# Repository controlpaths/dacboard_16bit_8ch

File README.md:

# 8CH DAC Board (16 bits)

Many times we need to obtain an analog signal from an embedded system. In these cases we will need a digital to analog converter. This board features two 4 channel digital to analog converters with a resolution of 16 bits. 

The output voltage of the board has a range from -10 volt to 10 volts qith a supply voltage of +-12V.

## Analog output

The DAC used in this board is the [DAC80004](https://www.ti.com/product/es-mx/DAC80004), a 4 channel, 16 bits DAC from Texas Instruments. This DAC is footprint compatible with DAC70004 (14 bits), and DAC60004 (12 bits).

To obtain the bipolar output, a simple circuit with just one amplifier is used. 

## Voltage reference

For the output range of +-10V, we will need a voltage reference of 2.5 volts. We can reduce the output range, and therefore increase the resolution in volts by using a reference of 1.024 volts or 1.250.

The reference used is the REF5020 with soma capacitors for fixeliminate the noise in the output voltage.

## Connectors

The conenctor are the only component in the bottom side of the board. The board uses three connectors, one for the control of the DAC, and two for the output voltages.

## Layout

The layout of the board is 35mm x 50mm. Several VCC planes and GND planes are used in the board to share the power supplies.

## Get Yours

This DAC Board is open-source, so you can use the output files to build your own in [JLCPCB](https://jlcpcb.com/?from=controlpath). You just need to compress the `gerber` directory, and upload it to [JLCPCB](https://jlcpcb.com/?from=controlpath). 

Remember to change the Surface Finish to **LeadFree HASL** to make your board ROHS compliant.

Then you have to add the PCB Assembly service and upload the [centroid](./kicad/production_files/dac16bit_8ch-all-pos.csv) file, and the [BOM](./kicad/production_files/bom.csv).

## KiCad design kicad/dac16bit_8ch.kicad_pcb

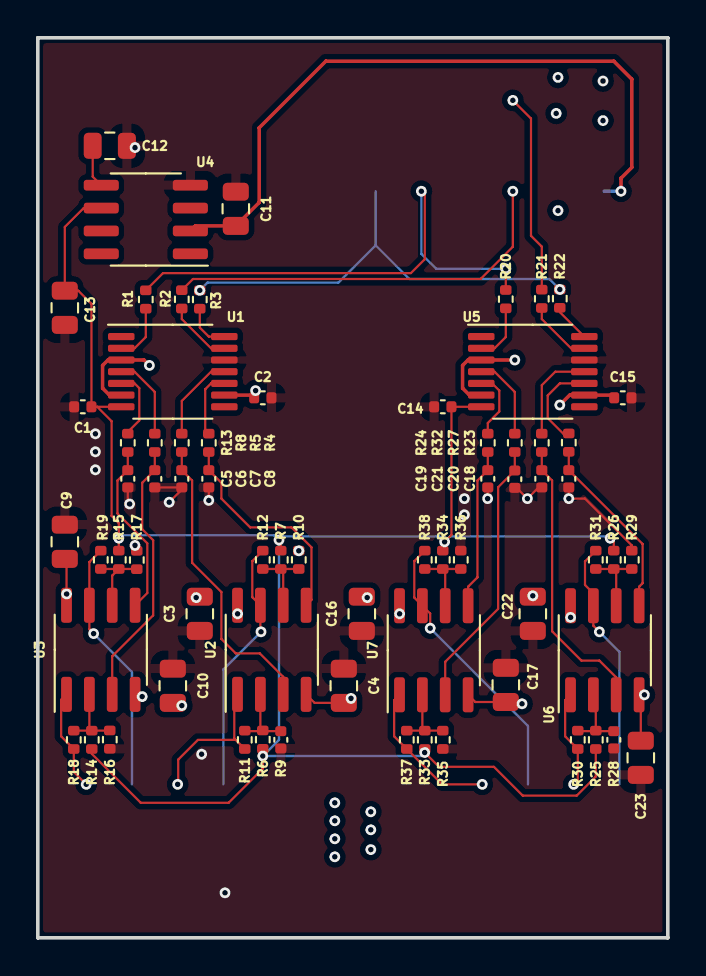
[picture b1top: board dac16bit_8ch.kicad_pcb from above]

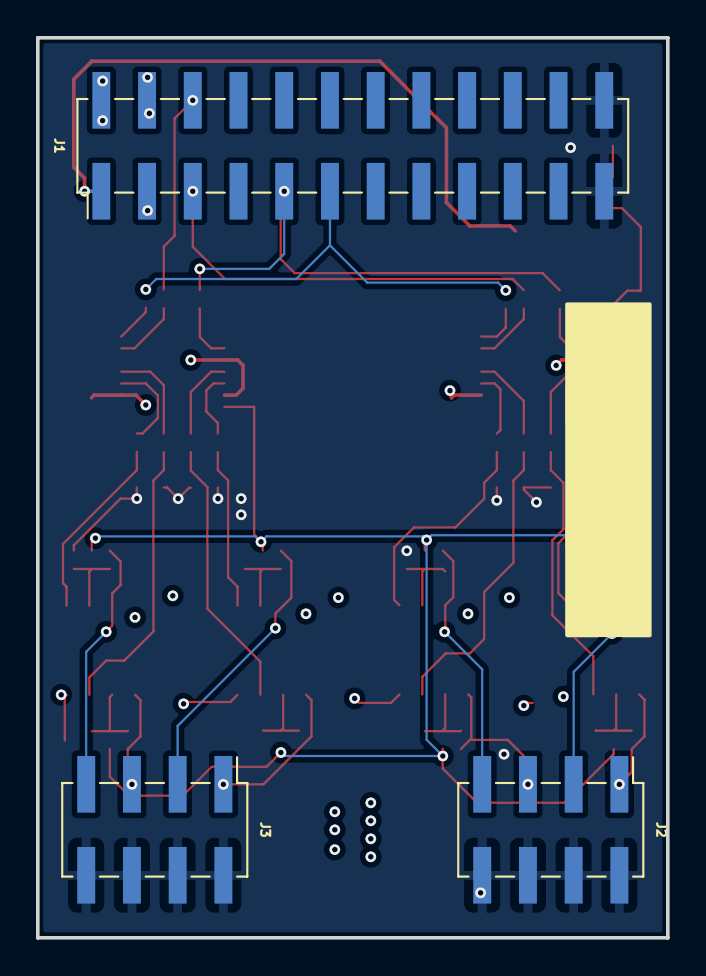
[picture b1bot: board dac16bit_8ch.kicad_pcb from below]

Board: 4 copper layers, 35.0 x 50.0 mm, 71 parts (3 on the bottom side), 49 nets.

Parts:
C1, C2, C14, C15: 100n; C_0402_1005Metric
C3, C4, C9, C10, C12, C16, C17, C22, C23: 100n; C_0805_2012Metric
C5, C6, C7, C8, C18, C19, C20, C21: 1n; C_0402_1005Metric
C11, C13: 1u; C_0805_2012Metric
J1: Conn_02x12_Odd_Even; PinHeader_2x12_P2.54mm_Vertical_SMD
J2, J3: Conn_02x04_Odd_Even; PinHeader_2x04_P2.54mm_Vertical_SMD
R1, R2, R3, R20, R21, R22: 100; R_0402_1005Metric
R4, R5, R8, R13, R23, R24, R27, R32: 4k7; R_0402_1005Metric
R6, R7, R14, R15, R25, R26, R33, R34: 8.25k; R_0402_1005Metric
R9, R28: 11k; C_0402_1005Metric
R10, R16, R17, R29, R35, R36: 11k; R_0402_1005Metric
R11, R12, R18, R19, R30, R31, R37, R38: 33k; R_0402_1005Metric
U1, U5: dacx0004; TSSOP-14_4.4x5mm_P0.65mm
U2, U3, U6, U7: OPA2188; SOIC-8_3.9x4.9mm_P1.27mm
U4: REF5025AD; SOIC-8_3.9x4.9mm_P1.27mm

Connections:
+3V3: C2.1, C15.1, J1.3, U1.3 (VDD), U1.6 (POR), U1.9 (~CLR), U5.3 (VDD), U5.6 (POR), U5.9 (~CLR)
+5V: C11.2, J1.1, U4.2 (Vin)
+12V: C3.2, C9.2, C16.2, C22.2, J1.2, U2.8 (V+), U3.8 (V+), U6.8 (V+), U7.8 (V+)
-12V: C4.2, C10.2, C17.2, C23.2, J1.4, U2.4 (V-), U3.4 (V-), U6.4 (V-), U7.4 (V-)
/dac0/vout_a_dac: C8.2, R13.2, U3.5 (+)
/dac0/vout_b_dac: C7.2, R8.2, U3.3 (+)
/dac0/vout_c_dac: C6.2, R5.2, U2.3 (+)
/dac0/vout_d_dac: C5.2, R4.2, U2.5 (+)
/dac1/vout_a_dac: C21.2, R32.2, U7.3 (+)
/dac1/vout_b_dac: C20.2, R27.2, U6.3 (+)
/dac1/vout_c_dac: C19.2, R24.2, U7.5 (+)
/dac1/vout_d_dac: C18.2, R23.2, U6.5 (+)
AO_CH0+: J2.1, R18.1, U3.1
AO_CH1+: J2.3, R19.1, U3.7
AO_CH2+: J2.5, R11.1, U2.1
AO_CH3+: J2.7, R12.1, U2.7
AO_CH4+: J3.1, R37.1, U7.1
AO_CH5+: J3.3, R38.1, U7.7
AO_CH6+: J3.5, R30.1, U6.1
AO_CH7+: J3.7, R31.1, U6.7
CLK_DAC: J1.11, R3.1, R22.1
CS_DAC: J1.9, R1.1, R20.1
GND: C1.2, C2.2, C3.1, C4.1, C5.1, C6.1, C7.1, C8.1, C9.1, C10.1, C11.1, C12.2, C13.2, C14.2, C15.2, C16.1, C17.1, C18.1, C19.1, C20.1, C21.1, C22.1, C23.1, J1.23, J1.24, J2.2, J2.4, J2.6, J2.8, J3.2, J3.4, J3.6, J3.8, R9.1, R10.1, R16.1, R17.1, R28.1, R29.1, R35.1, R36.1, U1.12 (GND), U4.4 (GND), U5.12 (GND)
unnamed: R3.2, U1.14 (SCLK)
unnamed: R2.2, U1.13 (SDIN)
unnamed: R8.1, U1.4 (VOUT_A)
unnamed: R5.1, U1.11 (VOUT_B)
unnamed: R13.1, U1.5 (VOUT_C)
unnamed: R4.1, U1.10 (VOUT_D)
unnamed: R1.2, U1.2 (~SYNC)
unnamed: R6.2, R9.2, R11.2, U2.2 (-)
unnamed: R7.2, R10.2, R12.2, U2.6 (-)
unnamed: R14.2, R16.2, R18.2, U3.2 (-)
unnamed: R15.2, R17.2, R19.2, U3.6 (-)
unnamed: C12.1, U4.5 (Trim/NR)
unnamed: R22.2, U5.14 (SCLK)
unnamed: R21.2, U5.13 (SDIN)
unnamed: R32.1, U5.4 (VOUT_A)
unnamed: R27.1, U5.11 (VOUT_B)
unnamed: R24.1, U5.5 (VOUT_C)
unnamed: R23.1, U5.10 (VOUT_D)
unnamed: R20.2, U5.2 (~SYNC)
unnamed: R25.2, R28.2, R30.2, U6.2 (-)
unnamed: R26.2, R29.2, R31.2, U6.6 (-)
unnamed: R33.2, R35.2, R37.2, U7.2 (-)
unnamed: R34.2, R36.2, R38.2, U7.6 (-)
RX_DAC0: J1.5, R2.1
RX_DAC1: J1.6, R21.1
VREF_DAC: C1.1, C13.1, C14.1, R6.1, R7.1, R14.1, R15.1, R25.1, R26.1, R33.1, R34.1, U1.7 (REFIN), U4.6 (Vout), U5.7 (REFIN)

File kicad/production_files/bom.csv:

Designator,Comment,Footprint,JLCPCB Part #
"C1,C2,C14,C15",100n,Capacitor_SMD:C_0402_1005Metric,
"C3,C4,C9,C10,C12,C16,C17,C22,C23",100n,Capacitor_SMD:C_0805_2012Metric,
"C5,C6,C7,C8,C18,C19,C20,C21",1n,Capacitor_SMD:C_0402_1005Metric,
"C11,C13",1u,Capacitor_SMD:C_0805_2012Metric,
J1,Conn_02x12_Odd_Even,Connector_PinHeader_2.54mm:PinHeader_2x12_P2.54mm_Vertical_SMD,
"J2,J3",Conn_02x04_Odd_Even,Connector_PinHeader_2.54mm:PinHeader_2x04_P2.54mm_Vertical_SMD,
"R1,R2,R3,R20,R21,R22",100,Resistor_SMD:R_0402_1005Metric,
"R4,R5,R8,R13,R23,R24,R27,R32",4k7,Resistor_SMD:R_0402_1005Metric,
"R6,R7,R14,R15,R25,R26,R33,R34",8.25k,Resistor_SMD:R_0402_1005Metric,
"R9,R28",11k,Capacitor_SMD:C_0402_1005Metric,
"R10,R16,R17,R29,R35,R36",11k,Resistor_SMD:R_0402_1005Metric,
"R11,R12,R18,R19,R30,R31,R37,R38",33k,Resistor_SMD:R_0402_1005Metric,
"U1,U5",dacx0004,Package_SO:TSSOP-14_4.4x5mm_P0.65mm,C2679895
"U2,U3,U6,U7",OPA2188,Package_SO:SOIC-8_3.9x4.9mm_P1.27mm,C17271
U4,REF5025AD,Package_SO:SOIC-8_3.9x4.9mm_P1.27mm,

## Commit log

2024-08-29 uploaded board
